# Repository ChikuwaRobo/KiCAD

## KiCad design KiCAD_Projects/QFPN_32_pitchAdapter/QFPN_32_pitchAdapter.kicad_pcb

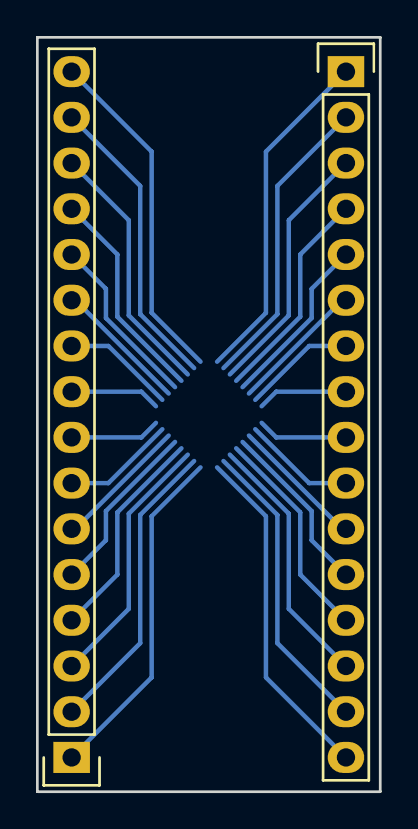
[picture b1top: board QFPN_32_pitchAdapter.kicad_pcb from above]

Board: 2 copper layers, 19.1 x 41.9 mm, 3 parts (1 on the bottom side), 32 nets.

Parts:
P1: CONN_01X32; QFN-32-1EP_5x5mm_Pitch0.5mm
P2, P3: CONN_01X16; Pin_Header_Straight_1x16

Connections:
unnamed: P1.1, P3.1
unnamed: P1.2, P3.2
unnamed: P1.3, P3.3
unnamed: P1.4, P3.4
unnamed: P1.5, P3.5
unnamed: P1.6, P3.6
unnamed: P1.7, P3.7
unnamed: P1.8, P3.8
unnamed: P1.9, P3.9
unnamed: P1.10, P3.10
unnamed: P1.11, P3.11
unnamed: P1.12, P3.12
unnamed: P1.13, P3.13
unnamed: P1.14, P3.14
unnamed: P1.15, P3.15
unnamed: P1.16, P3.16
unnamed: P1.17, P2.1
unnamed: P1.18, P2.2
unnamed: P1.19, P2.3
unnamed: P1.20, P2.4
unnamed: P1.21, P2.5
unnamed: P1.22, P2.6
unnamed: P1.23, P2.7
unnamed: P1.24, P2.8
unnamed: P1.25, P2.9
unnamed: P1.26, P2.10
unnamed: P1.27, P2.11
unnamed: P1.28, P2.12
unnamed: P1.29, P2.13
unnamed: P1.30, P2.14
unnamed: P1.31, P2.15
unnamed: P1.32, P2.16

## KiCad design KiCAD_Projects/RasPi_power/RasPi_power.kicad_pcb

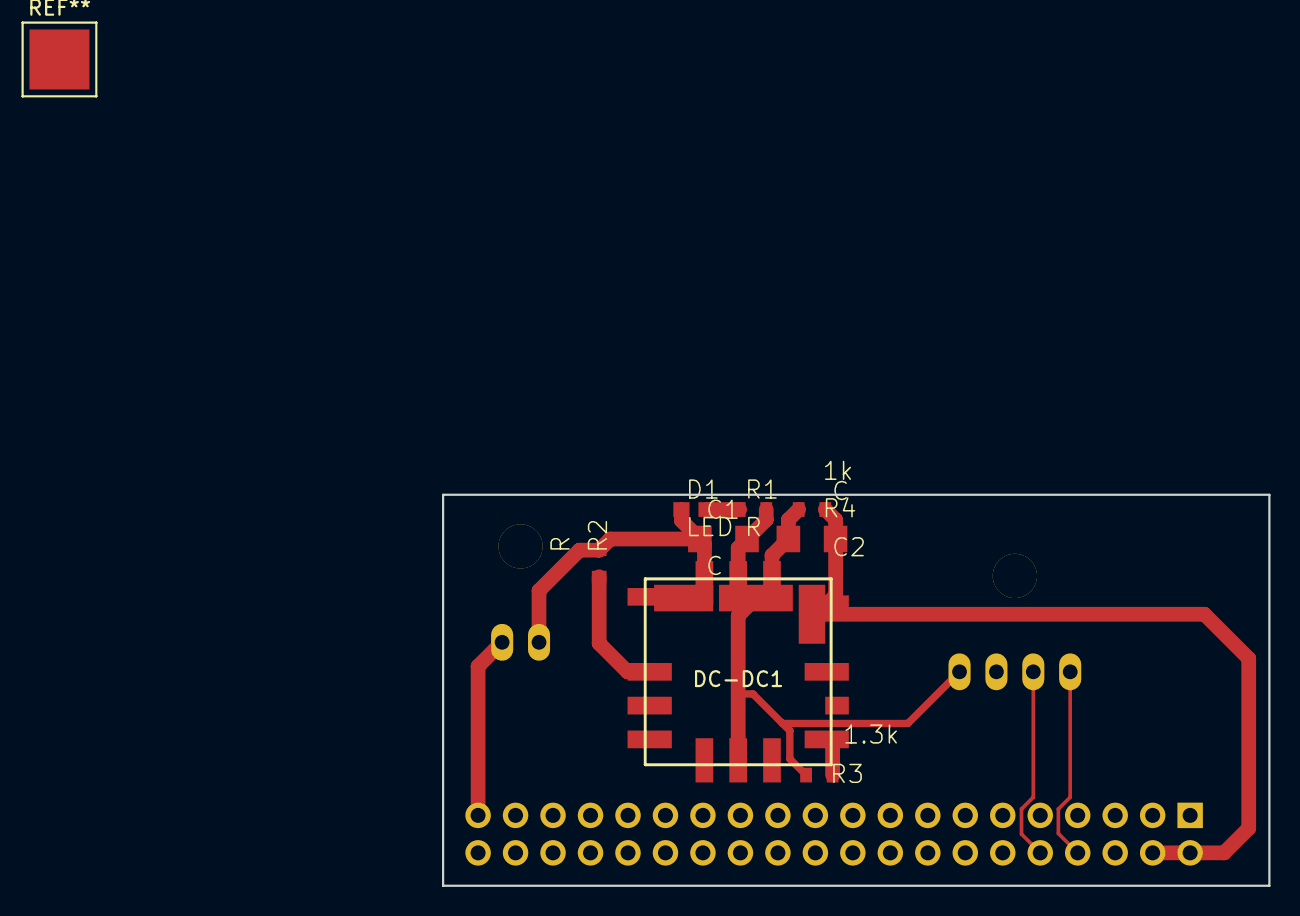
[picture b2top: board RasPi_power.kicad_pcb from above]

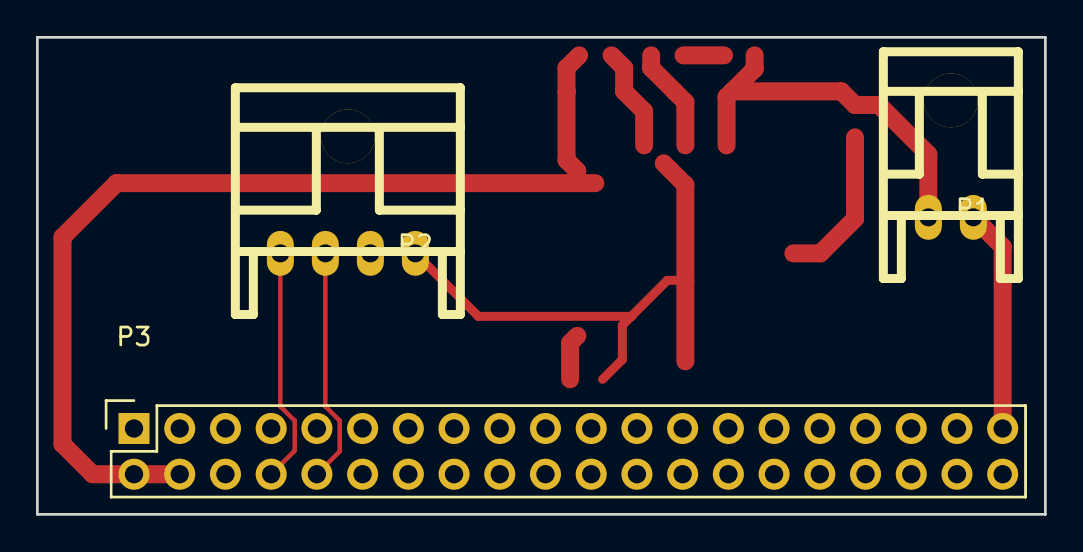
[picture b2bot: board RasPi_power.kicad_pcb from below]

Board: 2 copper layers, 56.0 x 26.5 mm, 11 parts (3 on the bottom side), 9 nets.

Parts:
C1, C2: C; C3216
D1: LED; C1608
DC-DC1: OKL-T3_series; OKL_T6
P1: CONN_01X02; XA_2LC
P2: CONN_01X04; XA_4LC
P3: CONN_02X20; Socket_Strip_Straight_2x20
R1, R2: R; C1608_WP
R3: 1.3k; C1608_WP
R4: 1k; C1608_WP

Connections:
/3.3V: P3.1, P3.17
/5V: C2.1, DC-DC1.4, DC-DC1.5, P3.2, P3.4, R4.1
/12V: C1.1, D1.1, DC-DC1.2, P1.2, R2.1
/GND: C1.2, C2.2, DC-DC1.3, DC-DC1.7, P1.1, P2.1, P3.6, P3.9, P3.14, P3.20, P3.25, P3.30, P3.34, P3.39, R1.2, R3.2, R4.2
/GPIO14: P2.4, P3.8
/GPIO15: P2.3, P3.10
unnamed: D1.2, R1.1
unnamed: DC-DC1.1, R2.2
unnamed: DC-DC1.6, R3.1

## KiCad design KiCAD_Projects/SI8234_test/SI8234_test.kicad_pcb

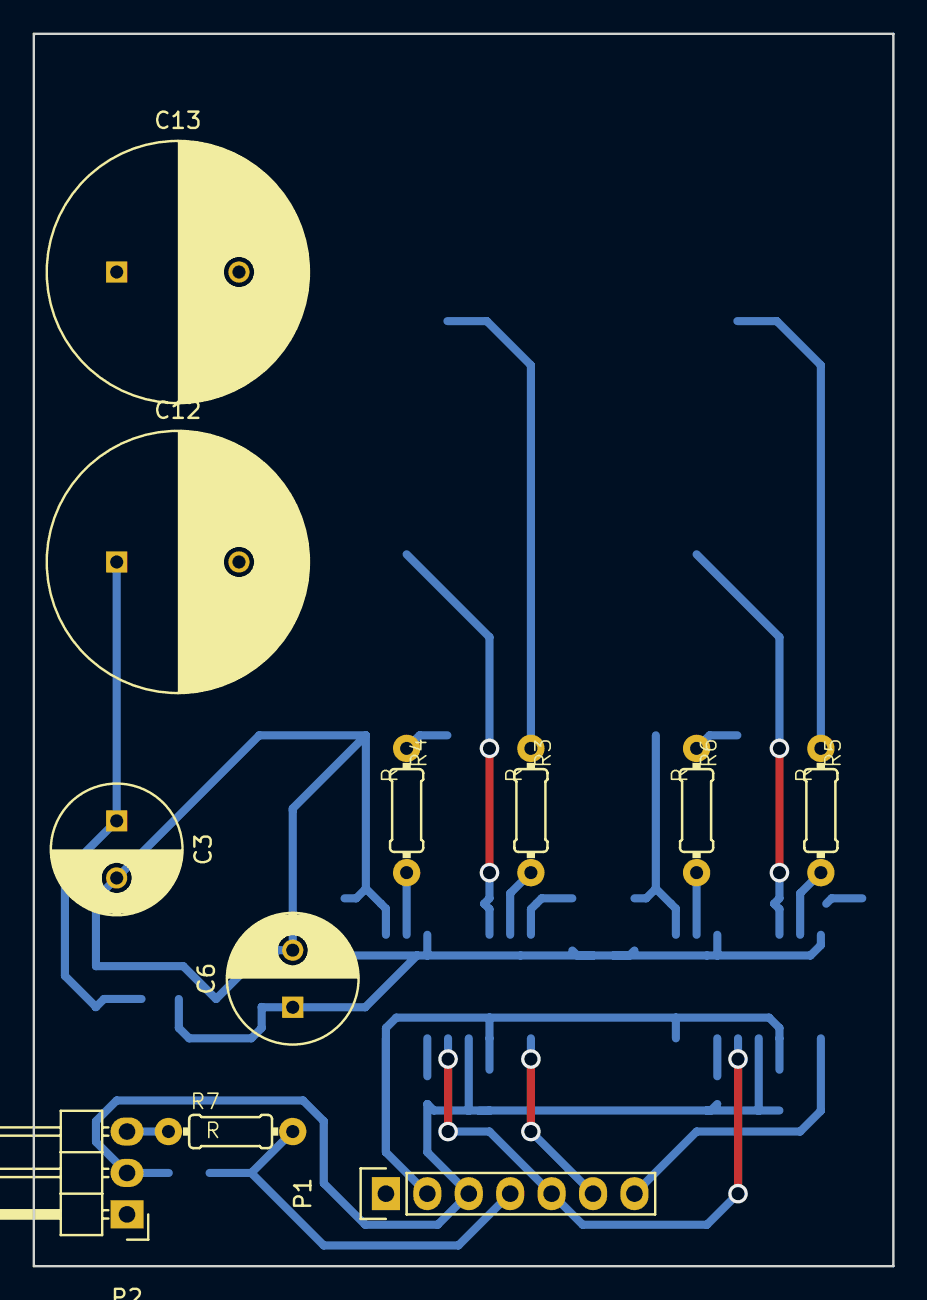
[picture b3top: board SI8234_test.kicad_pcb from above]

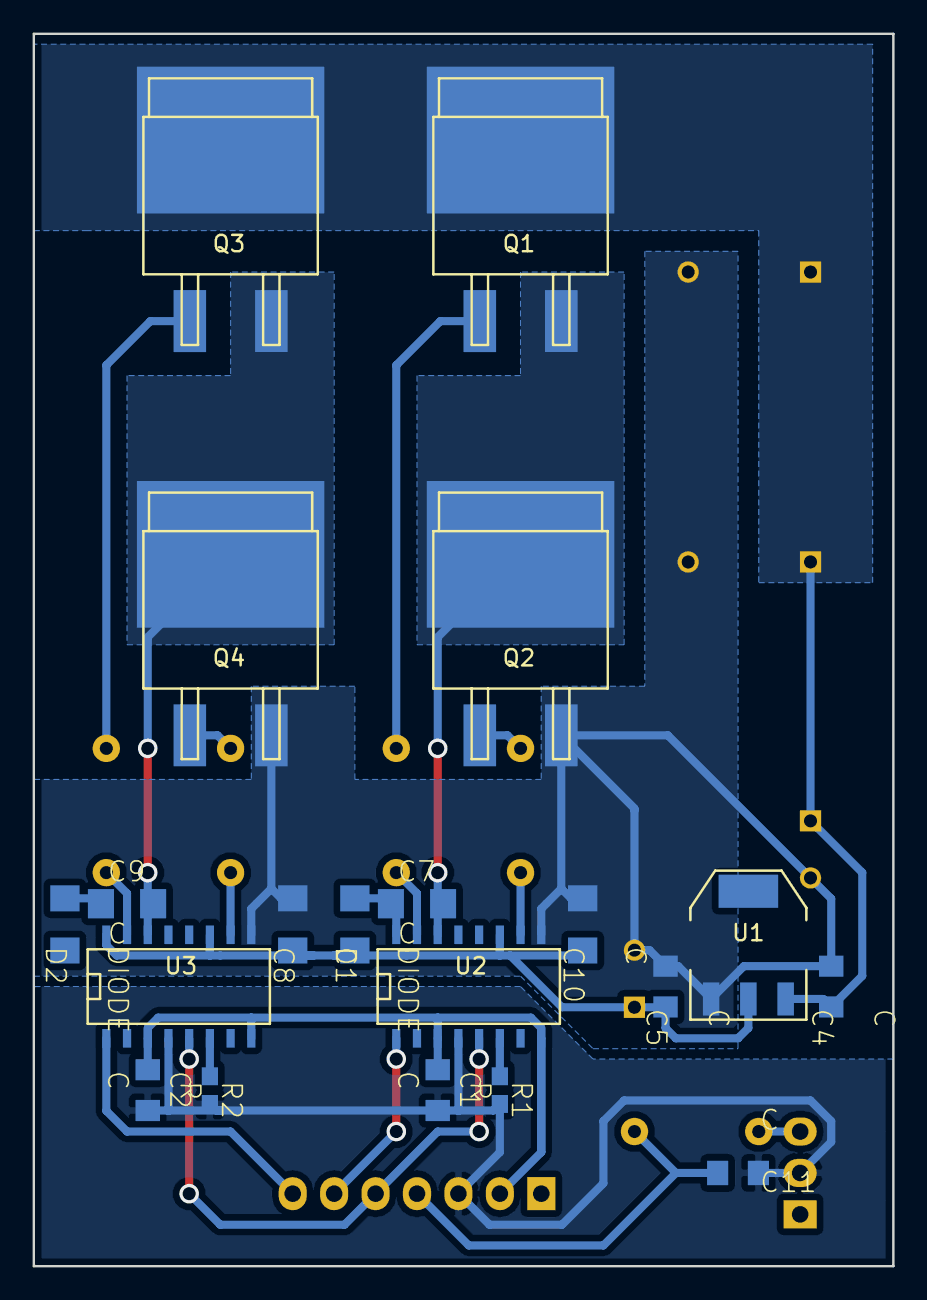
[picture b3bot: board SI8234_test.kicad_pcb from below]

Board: 2 copper layers, 52.7 x 75.6 mm, 31 parts (20 on the bottom side), 25 nets.

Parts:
C1, C2, C4, C5, C11: C; C2012
C3, C6: C; C_Radial_D8_L11.5_P3.5
C7, C8, C9, C10: C; C3216
C12, C13: C; C_Radial_D16_L30_P7.5
D1, D2: DIODE; C3216
P1: CONN_01X07; Pin_Header_Straight_1x07
P2: CONN_01X03; Pin_Header_Angled_1x03
Q1, Q2, Q3, Q4: MOSFET_N; D2-PAK
R1, R2: R; C1608
R3, R4, R5, R6, R7: R; 0204_2f7
U1: NCP1117ST12T3G; SOT-223
U2, U3: SI8234; SO-16-N

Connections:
+3.3V: P1.1, P2.1
+5V: C1.1, C2.1, P1.2, U2.3, U2.8, U3.3, U3.8
+BATT: C3.1, C4.1, C12.1, C13.1, Q1.D, Q3.D, U1.3
/Current: C11.2, P1.4, R7.2
/GD_PS: C5.1, C6.1, C8.1, C10.1, D1.1, D2.1, U1.2, U2.11, U3.11
/PWM_A: P1.6, U2.1
/PWM_B: P1.7, U3.1
/~EN: P1.5, U2.5, U3.5
GND: C1.2, C2.2, C11.1, P1.3, P2.2, R2.2, U2.4, U3.4
GNDPWR: C3.2, C4.2, C5.2, C6.2, C8.2, C10.2, C12.2, C13.2, Q2.S, Q4.S, U1.1, U2.9, U3.9
unnamed: C7.1, D1.2, U2.16
unnamed: C7.2, Q1.S, Q2.D, U2.14
unnamed: C9.1, D2.2, U3.16
unnamed: C9.2, Q3.S, Q4.D, U3.14
unnamed: P2.3, R7.1
unnamed: Q1.G, R3.1
unnamed: Q2.G, R4.1
unnamed: Q3.G, R5.1
unnamed: Q4.G, R6.1
unnamed: R1.1, U2.6
unnamed: R2.1, U3.6
unnamed: R3.2, U2.15
unnamed: R4.2, U2.10
unnamed: R5.2, U3.15
unnamed: R6.2, U3.10

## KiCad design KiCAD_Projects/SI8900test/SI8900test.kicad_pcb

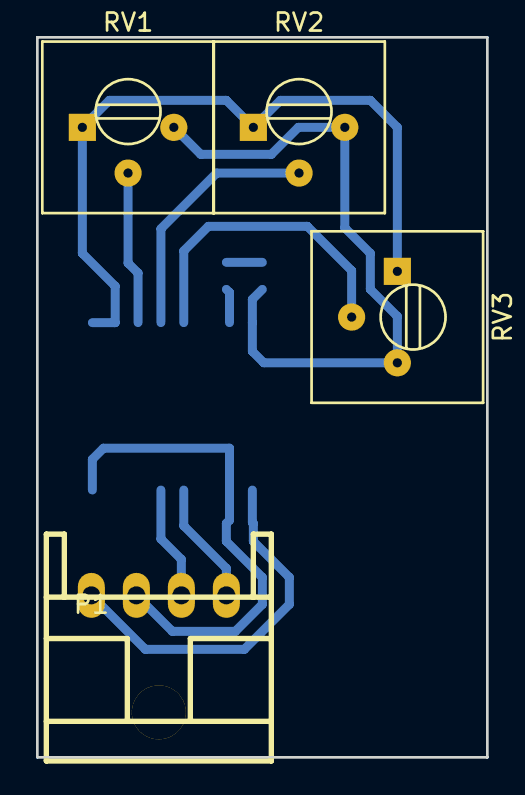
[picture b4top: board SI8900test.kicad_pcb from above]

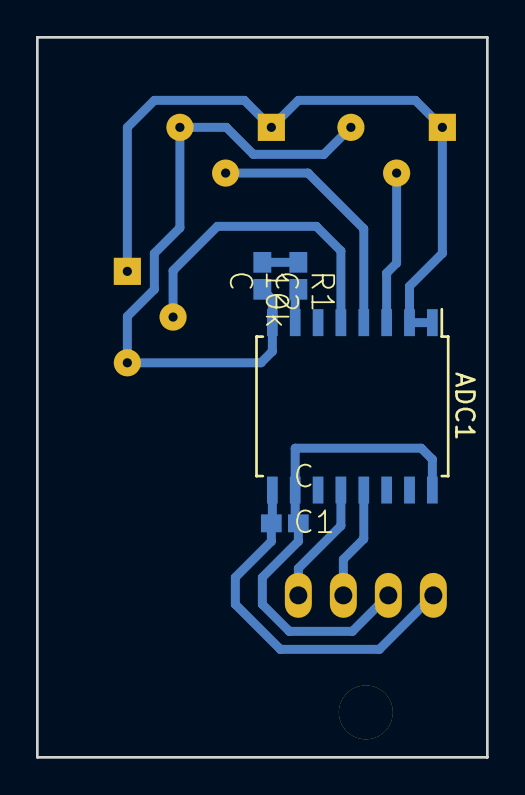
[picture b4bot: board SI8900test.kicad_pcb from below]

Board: 2 copper layers, 25.0 x 40.0 mm, 8 parts (4 on the bottom side), 8 nets.

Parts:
ADC1: Si8900; SOIC-16_7.5x10.3mm_Pitch1.27mm
C1, C2: C; C1608_NP
P1: CONN_01X04; XA_4LC
R1: 10k; C1608_NP
RV1, RV2, RV3: POT; Potentiometer_Trimmer-Suntan-TSR-3386P

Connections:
+3.3V: ADC1.1, ADC1.2, ADC1.10, ADC1.16, C1.1, C2.1, P1.2, R1.1, RV1.1, RV2.1, RV3.1
/IN0: ADC1.3, RV1.2
/IN1: ADC1.4, RV2.2
/IN2: ADC1.5, RV3.2
/RX: ADC1.13, P1.3
/TX: ADC1.12, P1.4
GND: ADC1.8, ADC1.9, C1.2, C2.2, P1.1, RV1.3, RV2.3, RV3.3
unnamed: ADC1.7, R1.2

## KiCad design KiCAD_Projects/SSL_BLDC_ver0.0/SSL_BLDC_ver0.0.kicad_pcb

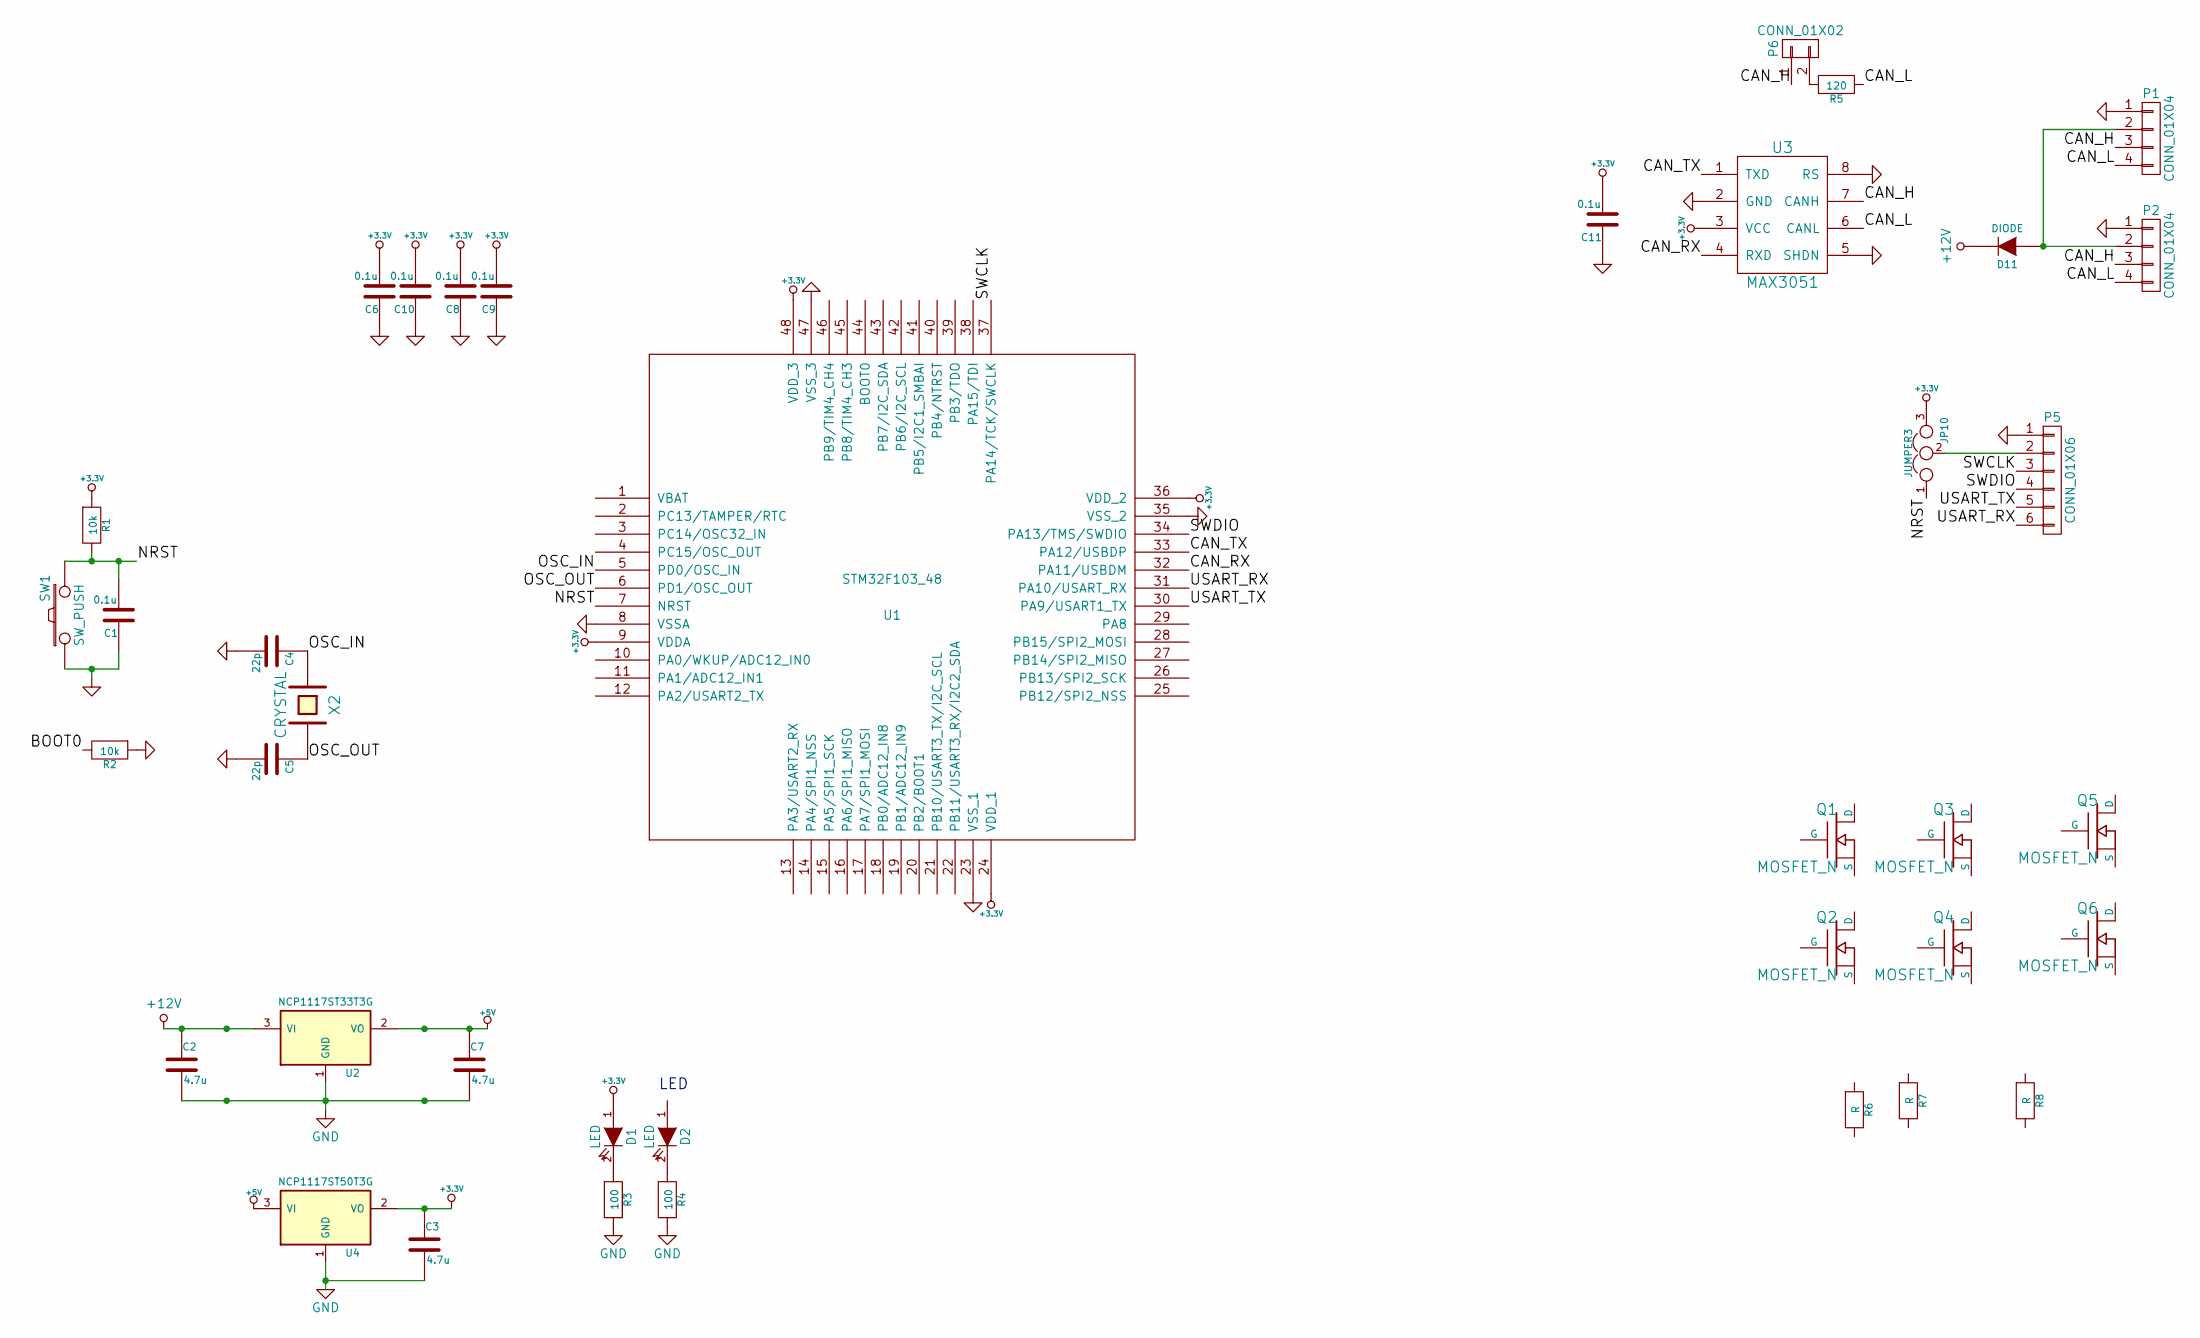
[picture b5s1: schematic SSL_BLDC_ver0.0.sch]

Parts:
C1, C6, C8, C9, C10, C11: 0.1u; C1608_WP
C2, C3, C7: 4.7u; C2012
C4, C5: 22p; C1608_WP
D1, D2: LED; LED_0805
D11: DIODE; SMA_Standard
JP10: JUMPER3; GS3
P1, P2: CONN_01X04; XA_4T
P5: CONN_01X06; ZH_6T
P6: CONN_01X02; Pin_Header_Straight_1x02
Q1, Q2, Q3, Q4, Q5, Q6: MOSFET_N; SOT-428_GDS_compact
R1, R2: 10k; C1608_WP
R3, R4: 100; C1608_WP
R5: 120; C1608_WP
R6, R7, R8: R; R_2010
SW1: SW_PUSH; SW_SPST_EVQPE1
U1: STM32F103_48; LQFP-48_7x7mm_Pitch0.5mm
U2: NCP1117ST33T3G; SOT-223_reg
U3: MAX3051; SOIC-8_3.9x4.9mm_Pitch1.27mm
U4: NCP1117ST50T3G; SOT-223_reg
X2: CRYSTAL; ABM3_2pads

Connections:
+3.3V: C3.1, C6.2, C8.2, C9.2, C10.2, C11.2, D1.1 (A), JP10.3, R1.1, U1.9 (VDDA), U1.24 (VDD_1), U1.36 (VDD_2), U1.48 (VDD_3), U3.3 (VCC), U4.2 (VO)
+5V: C7.1, U2.2 (VO), U4.3 (VI)
+12V: C2.1, D11.1 (K), U2.3 (VI)
/CAN_H: P1.3, P2.3, P6.1, U3.7 (CANH)
/CAN_L: P1.4, P2.4, R5.1, U3.6 (CANL)
/CAN_RX: U1.32 (PA11/USBDM), U3.4 (RXD)
/CAN_TX: U1.33 (PA12/USBDP), U3.1 (TXD)
/NRST: C1.2, JP10.1, R1.2, SW1.2, U1.7 (NRST)
/OSC_IN: C4.1, U1.5 (PD0/OSC_IN), X2.1
/OSC_OUT: C5.1, U1.6 (PD1/OSC_OUT), X2.2
/SWCLK: P5.3, U1.37 (PA14/TCK/SWCLK)
/SWDIO: P5.4, U1.34 (PA13/TMS/SWDIO)
/USART_RX: P5.6, U1.31 (PA10/USART_RX)
/USART_TX: P5.5, U1.30 (PA9/USART1_TX)
GND: C1.1, C2.2, C3.2, C4.2, C5.2, C6.1, C7.2, C8.1, C9.1, C10.1, C11.1, P1.1, P2.1, P5.1, R2.1, R3.2, R4.2, SW1.1, U1.8 (VSSA), U1.23 (VSS_1), U1.35 (VSS_2), U1.47 (VSS_3), U2.1 (GND), U3.2 (GND), U3.5 (SHDN), U3.8 (RS), U4.1 (GND)
unnamed: D1.2 (K), R3.1
unnamed: D2.2 (K), R4.1
unnamed: D11.2 (A), P1.2, P2.2
unnamed: JP10.2, P5.2
unnamed: P6.2, R5.2

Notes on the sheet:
LED

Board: 2 copper layers, 39 parts (15 on the bottom side), 20 nets, no tracks yet.

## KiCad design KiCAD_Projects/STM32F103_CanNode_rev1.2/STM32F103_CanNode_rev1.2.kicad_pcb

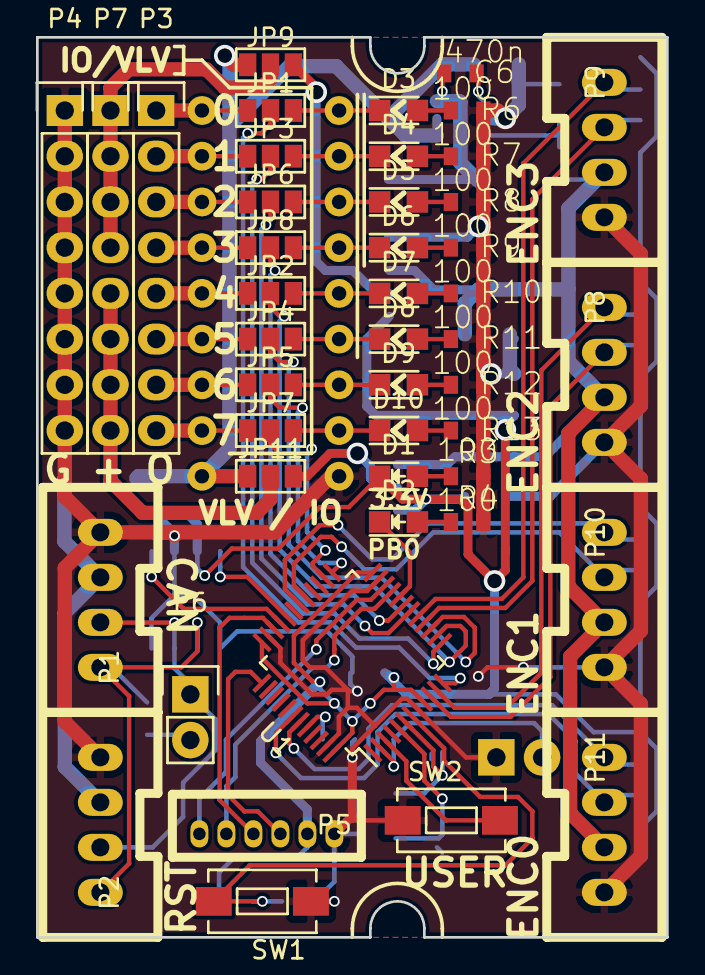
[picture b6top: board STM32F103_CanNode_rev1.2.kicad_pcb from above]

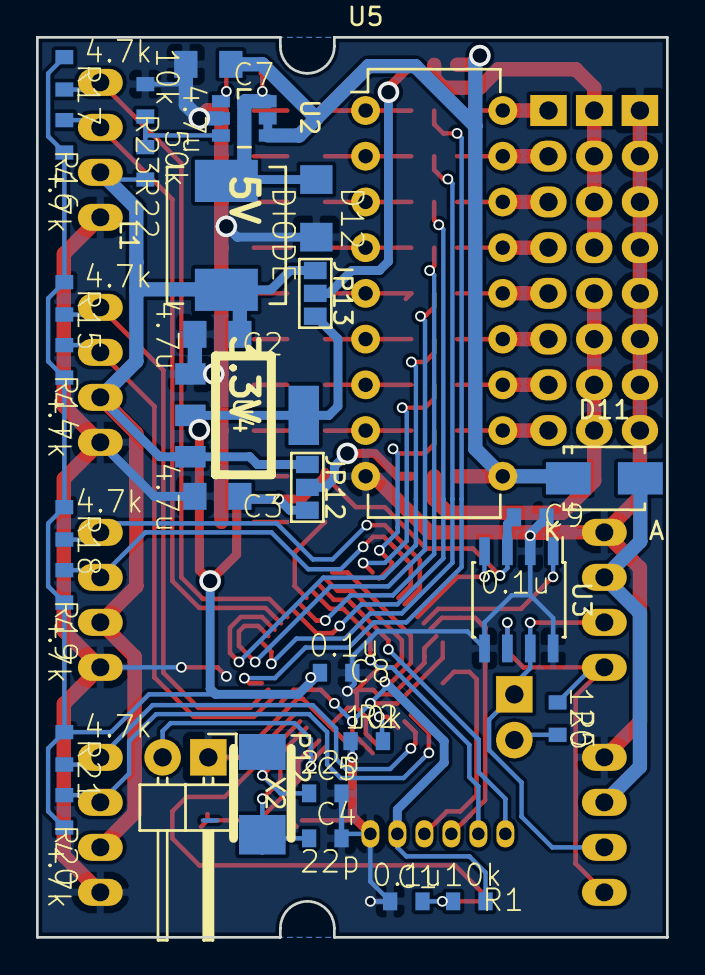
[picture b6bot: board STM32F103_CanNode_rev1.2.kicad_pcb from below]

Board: 2 copper layers, 35.0 x 50.0 mm, 77 parts (32 on the bottom side), 70 nets.

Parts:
C1, C8, C9: 0.1u; C1608_WP
C2, C3, C7: 4.7u; C2012
C4, C5: 22p; C1608_WP
C6: 470n; C1608_WP
D1, D2, D3, D4, D5, D6, D7, D8, D9, D10: LED; LED_0805
D11: DIODE; SMA_Standard
D12: DIODE; C3216
JP1, JP2, JP3, JP4, JP5, JP6, JP7, JP8, JP9, JP11, JP12, JP13: JUMPER3; GS3
L1: 2.2u; Neosid_Inductor_SM-PIC0602H
P1, P2, P8, P9, P10, P11: CONN_01X04; XA_4T
P3, P4, P7: CONN_01X08; Pin_Header_Straight_1x08
P5: CONN_01X06; ZH_6T
P6: CONN_01X02; Pin_Header_Straight_1x02
P12: CONN_01X02; Pin_Header_Angled_1x02
R1, R2, R23: 10k; C1608_WP
R3, R4, R6, R7, R8, R9, R10, R11, R12, R13: 100; C1608_WP
R5: 120; C1608_WP
R14, R15, R16, R17, R18, R19, R20, R21: 4.7k; C1608_WP
R22: 50k; C1608_WP
SW1, SW2: SW_PUSH; SW_SPST_EVQPE1
U1: STM32F103_48; LQFP-48_7x7mm_Pitch0.5mm
U2: AOZ1280; TSOT-6-MK06A
U3: MAX3051; SOIC-8_3.9x4.9mm_Pitch1.27mm
U4: NCP1117ST50T3G; SOT-223_reg
U5: TBD62083A; DIP-18_W7.62mm
X2: CRYSTAL; ABM3_2pads

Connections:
+3.3V: C3.1, C8.2, C9.2, D1.1, JP12.3, JP13.3, P5.2, R1.1, R14.1, R15.1, R16.1, R17.1, R18.1, R19.1, R20.1, R21.1, U1.9, U1.24, U1.36, U1.48, U3.3, U4.2
+5V: C2.1, JP12.1, JP13.1, L1.1, P8.2, P9.2, P10.2, P11.2, R22.1, U4.3
+12V: C7.1, D11.1, JP9.1, JP11.1, U2.4, U2.5, U5.10
/BOOT0: R2.2, U1.44
/CAN_H: P1.3, P2.3, P6.1, U3.7
/CAN_L: P1.4, P2.4, R5.1, U3.6
/CAN_RX: U1.32, U3.4
/CAN_TX: U1.33, U3.1
/DCDC_FB: R22.2, R23.1, U2.3
/IO1: JP1.1, P3.1, U5.18
/IO2: JP3.1, P3.2, U5.17
/IO3: JP6.1, P3.3, U5.16
/IO4: JP8.1, P3.4, U5.15
/IO5: JP2.1, P3.5, U5.14
/IO6: JP4.1, P3.6, U5.13
/IO7: JP5.1, P3.7, U5.12
/IO8: JP7.1, P3.8, U5.11
/NRST: C1.2, R1.2, SW1.2, U1.7
/OSC_IN: C4.1, U1.5, X2.1
/OSC_OUT: C5.1, U1.6, X2.2
/OUT1: D3.1, JP1.3, U5.1
/OUT2: D4.1, JP3.3, U5.2
/OUT3: D5.1, JP6.3, U5.3
/OUT4: D6.1, JP8.3, U5.4
/OUT5: D7.1, JP2.3, U5.5
/OUT6: D8.1, JP4.3, U5.6
/OUT7: D9.1, JP5.3, U5.7
/OUT8: D10.1, JP7.3, U5.8
/PA0: P8.3, R14.2, U1.10
/PA1: P8.4, R15.2, U1.11
/PA2: JP1.2, U1.12
/PA3: JP3.2, U1.13
/PA4: JP2.2, U1.14
/PA5: JP4.2, U1.15
/PA6: P9.3, R16.2, U1.16
/PA7: P9.4, R17.2, U1.17
/PA8: P10.3, R19.2, U1.29
/PA9: P10.4, R18.2, U1.30
/PB0: JP6.2, U1.18
/PB1: JP8.2, U1.19
/PB2: D2.1, U1.20
/PB6: P11.3, R20.2, U1.42
/PB7: P11.4, R21.2, U1.43
/PB12: JP5.2, U1.25
/PB13: JP7.2, U1.26
/PC13: P12.2, U1.2
/PC14: SW2.2, U1.3
/SWCLK: P5.3, U1.37
/SWDIO: P5.4, U1.34
/USART_RX: P5.6, U1.22
/USART_TX: P5.5, U1.21
GND: C1.1, C2.2, C3.2, C4.2, C5.2, C7.2, C8.1, C9.1, D12.2, P1.1, P2.1, P4.1, P4.2, P4.3, P4.4, P4.5, P4.6, P4.7, P4.8, P5.1, P8.1, P9.1, P10.1, P11.1, P12.1, R2.1, R3.2, R4.2, R6.1, R7.1, R8.1, R9.1, R10.1, R11.1, R12.1, R13.1, R23.2, SW1.1, SW2.1, U1.8, U1.23, U1.35, U1.47, U2.2, U3.2, U3.5, U3.8, U4.1, U5.9
unnamed: C6.1, U2.1
unnamed: C6.2, D12.1, L1.2, U2.6
unnamed: D1.2, R3.1
unnamed: D2.2, R4.1
unnamed: D3.2, R6.2
unnamed: D4.2, R7.2
unnamed: D5.2, R8.2
unnamed: D6.2, R9.2
unnamed: D7.2, R10.2
unnamed: D8.2, R11.2
unnamed: D9.2, R12.2
unnamed: D10.2, R13.2
unnamed: D11.2, P1.2, P2.2
unnamed: JP9.2, P7.1, P7.2, P7.3, P7.4
unnamed: JP11.2, P7.5, P7.6, P7.7, P7.8
unnamed: JP11.3, JP12.2
unnamed: JP9.3, JP13.2
unnamed: P6.2, R5.2

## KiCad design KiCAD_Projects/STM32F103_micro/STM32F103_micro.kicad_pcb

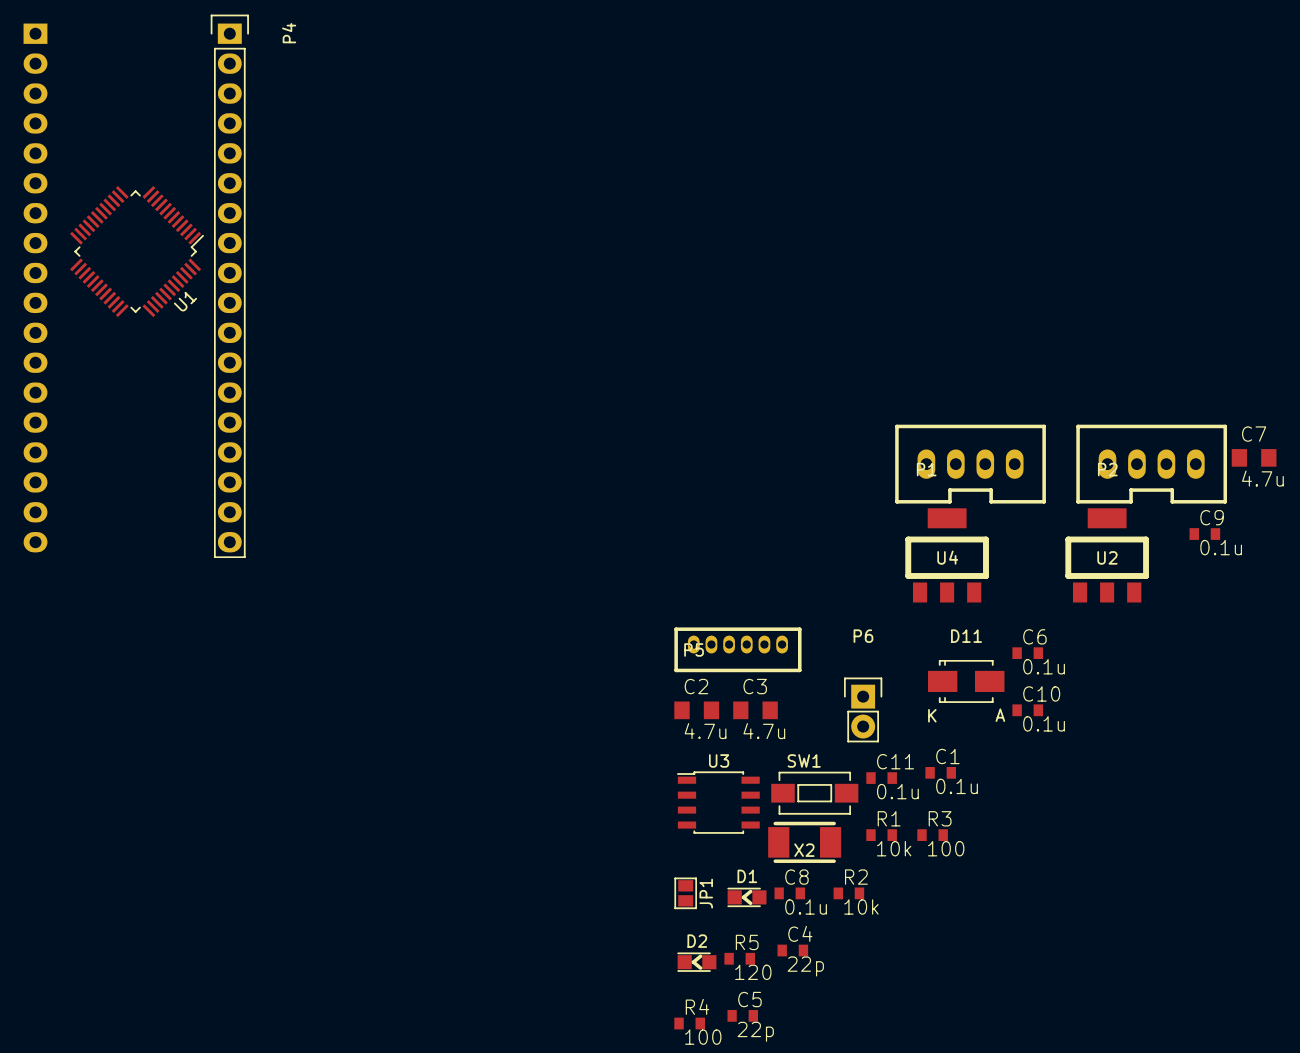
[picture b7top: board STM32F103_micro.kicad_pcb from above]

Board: 2 copper layers, 32 parts (1 on the bottom side), 47 nets, no tracks yet.

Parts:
C1, C6, C8, C9, C10, C11: 0.1u; C1608_WP
C2, C3, C7: 4.7u; C2012
C4, C5: 22p; C1608_WP
D1, D2: LED; LED_0805
D11: DIODE; SMA_Standard
JP1: JUMPER; GS2
P1, P2: CONN_01X04; XA_4T
P3, P4: CONN_01X18; Socket_Strip_Straight_1x18
P5: CONN_01X06; ZH_6T
P6: CONN_01X02; Pin_Header_Straight_1x02
R1, R2: 10k; C1608_WP
R3, R4: 100; C1608_WP
R5: 120; C1608_WP
SW1: SW_PUSH; SW_SPST_EVQPE1
U1: STM32F103_48; LQFP-48_7x7mm_Pitch0.5mm
U2: NCP1117ST33T3G; SOT-223_reg
U3: MAX3051; SOIC-8_3.9x4.9mm_Pitch1.27mm
U4: NCP1117ST50T3G; SOT-223_reg
X2: CRYSTAL; ABM3_2pads

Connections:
+3.3V: C3.1, C6.2, C8.2, C9.2, C10.2, C11.2, D1.1, P4.2, P5.2, R1.1, U1.1, U1.9, U1.24, U1.36, U1.48, U3.3, U4.2
+5V: C7.1, P4.3, U2.2, U4.3
+12V: C2.1, D11.1, P4.4, U2.3
/BOOT0: R2.2, U1.44
/CAN_H: P1.3, P2.3, P4.6, P6.1, U3.7
/CAN_L: P1.4, P2.4, P4.5, R5.1, U3.6
/CAN_RX: P4.9, U1.32, U3.4
/CAN_TX: P4.10, U1.33, U3.1
/LED: JP1.2, P3.11, U1.20
/NRST: C1.2, R1.2, SW1.2, U1.7
/OSC_IN: C4.1, U1.5, X2.1
/OSC_OUT: C5.1, U1.6, X2.2
/PA3: P3.4, U1.13
/PA4: P3.5, U1.14
/PA5: P3.6, U1.15
/PA6: P3.7, U1.16
/PA7: P3.8, U1.17
/PA8: P3.18, U1.29
/PA15: P4.11, U1.38
/PB0: P3.9, U1.18
/PB1: P3.10, U1.19
/PB3: P4.12, U1.39
/PB4: P4.13, U1.40
/PB5: P4.14, U1.41
/PB6: P4.15, U1.42
/PB7: P4.16, U1.43
/PB8: P4.18, U1.45
/PB9: P4.17, U1.46
/PB10: P3.12, U1.21
/PB11: P3.13, U1.22
/PB12: P3.14, U1.25
/PB13: P3.15, U1.26
/PB14: P3.16, U1.27
/PB15: P3.17, U1.28
/PC13: P3.1, U1.2
/PC14: P3.2, U1.3
/PC15: P3.3, U1.4
/SWCLK: P5.3, U1.37
/SWDIO: P5.4, U1.34
/USART_RX: P4.8, P5.6, U1.31
/USART_TX: P4.7, P5.5, U1.30
GND: C1.1, C2.2, C3.2, C4.2, C5.2, C6.1, C7.2, C8.1, C9.1, C10.1, C11.1, P1.1, P2.1, P4.1, P5.1, R2.1, R3.2, R4.2, SW1.1, U1.8, U1.23, U1.35, U1.47, U2.1, U3.2, U3.5, U3.8, U4.1
unnamed: D1.2, R3.1
unnamed: D2.1, JP1.1
unnamed: D2.2, R4.1
unnamed: D11.2, P1.2, P2.2
unnamed: P6.2, R5.2
